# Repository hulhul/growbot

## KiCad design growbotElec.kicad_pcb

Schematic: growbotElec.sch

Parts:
BatteryScrew1: Screw_Terminal_01x02; PinSocket_1x02_P1.27mm_Vertical
J1, J2, J3: Screw_Terminal_01x02; PinSocket_1x02_P1.27mm_Vertical
J4: Screw_Terminal_01x03; PinSocket_1x03_P1.27mm_Vertical
MK1, MK2, MK3, MK4: M2.5; PinSocket_1x01_P1.27mm_Vertical
P1: Conn_02x20_Odd_Even; PinSocket_2x20_P2.54mm_Vertical
U1, U2: L293D; DIP-16_W7.62mm

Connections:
+BATT: BatteryScrew1.2, J4.2, U1.8 (VCC2), U2.8 (VCC2)
-BATT: BatteryScrew1.1, J4.1, P1.6, P1.9, P1.14, P1.20, P1.25, P1.30, P1.34, P1.39, P1.40, U1.4 (GND), U1.5 (GND), U1.12 (GND), U1.13 (GND), U2.1 (EN1,2), U2.4 (GND), U2.5 (GND), U2.12 (GND), U2.13 (GND)
/GPIO2(SDA1): P1.3
/GPIO3(SCL1): P1.5
/GPIO4(GCLK): P1.7
/GPIO5: P1.29
/GPIO6: P1.31
/GPIO7(SPI1_CE_N): P1.26
/GPIO8(SPI0_CE_N): P1.24
/GPIO9(SPI0_MISO): P1.21
/GPIO10(SPI0_MOSI): P1.19
/GPIO11(SPI0_SCK): P1.23
/GPIO12(PWM0): J4.3, P1.32
/GPIO13(PWM1): P1.33
/GPIO14(TXD0): P1.8
/GPIO15(RXD0): P1.10
/GPIO16: P1.36, U2.7 (2A)
/GPIO17(GEN0): P1.11, U1.9 (EN3,4)
/GPIO18(GEN1)(PWM0): P1.12
/GPIO19(SPI1_MISO): P1.35
/GPIO20(SPI1_MOSI): P1.38, U2.2 (1A)
/GPIO22(GEN3): P1.15, U1.15 (4A)
/GPIO23(GEN4): P1.16, U1.7 (2A)
/GPIO24(GEN5): P1.18, U1.2 (1A)
/GPIO25(GEN6): P1.22, U1.1 (EN1,2)
/GPIO26: P1.37
/GPIO27(GEN2): P1.13, U1.10 (3A)
/ID_SC: P1.28
/ID_SD: P1.27
unnamed: J1.1, U1.3 (1Y)
unnamed: J1.2, U1.6 (2Y)
unnamed: J2.1, U1.11 (3Y)
unnamed: J2.2, U1.14 (4Y)
unnamed: J3.1, U2.3 (1Y)
unnamed: J3.2, U2.6 (2Y)
unnamed: P1.2, U1.16 (VCC1)
unnamed: P1.4, U2.16 (VCC1)

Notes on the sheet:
ID_SD and ID_SC PINS: These pins are reserved for HAT ID EEPROM. At boot time this I2C interface will be interrogated to look for an EEPROM that identifes the attached board and allows automagic setup of the GPIOs (and optionally, Linux drivers). DO NOT USE these pins for anything other than attach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
Mounting Holes

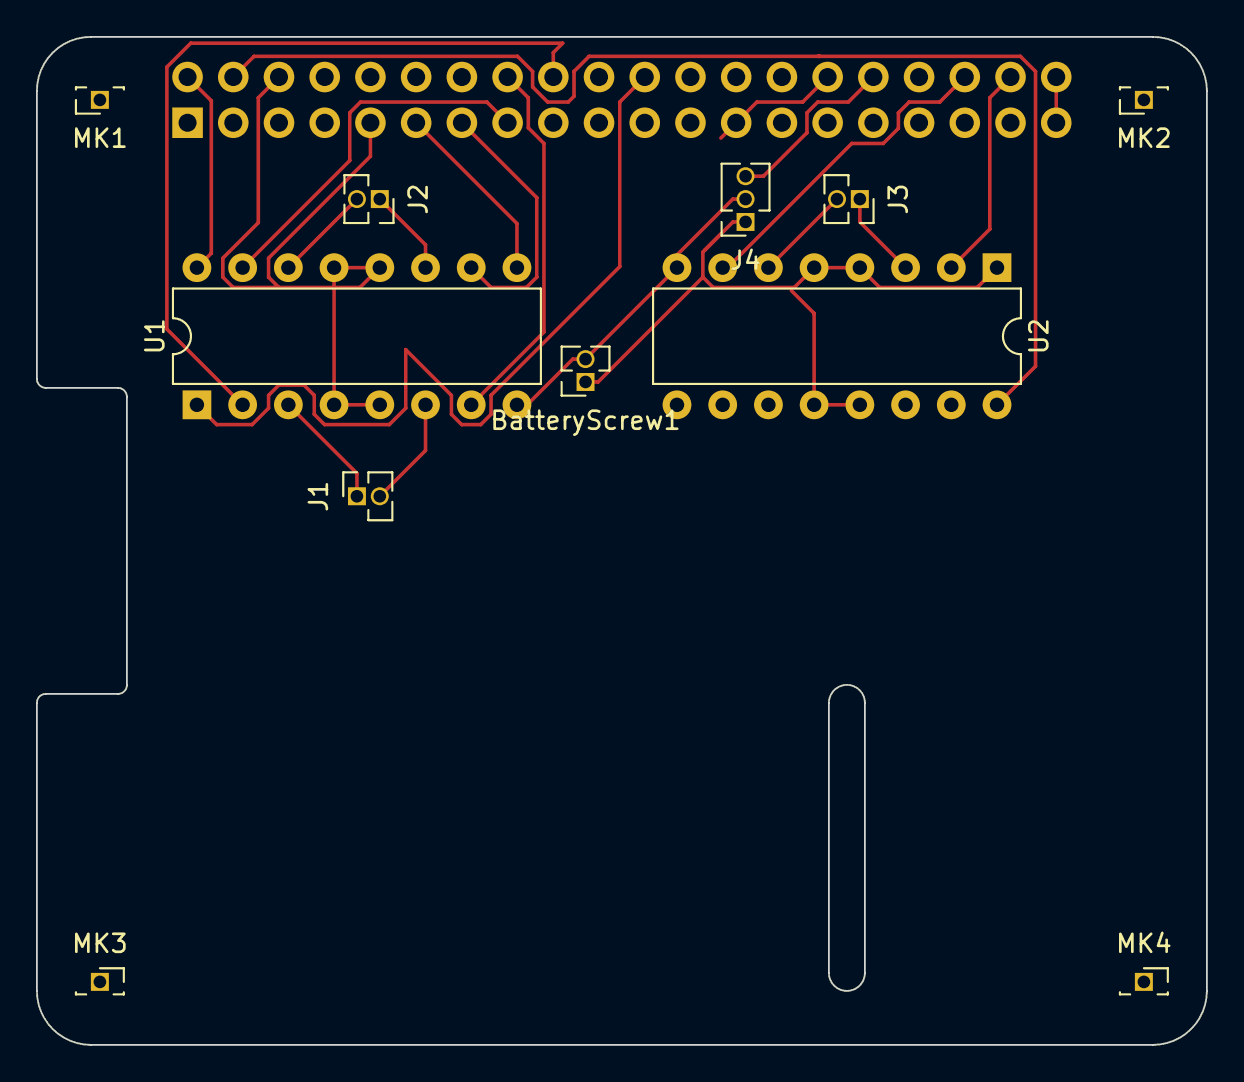
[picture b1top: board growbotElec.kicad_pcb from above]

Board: 2 copper layers, 65.0 x 56.0 mm, 12 parts (1 on the bottom side), 19 nets.
